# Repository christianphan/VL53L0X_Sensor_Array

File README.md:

# VL53L0X_Sensor_Array
Schematic and Cad file for array of VL53L0X for proximity sensing applications

This PCB combines 5 VL53L0X sensors adjacent next to each other to detect motion and finger gestures. An I2C multiplexor is also in the PCB to control the 5 sensors over I2C.

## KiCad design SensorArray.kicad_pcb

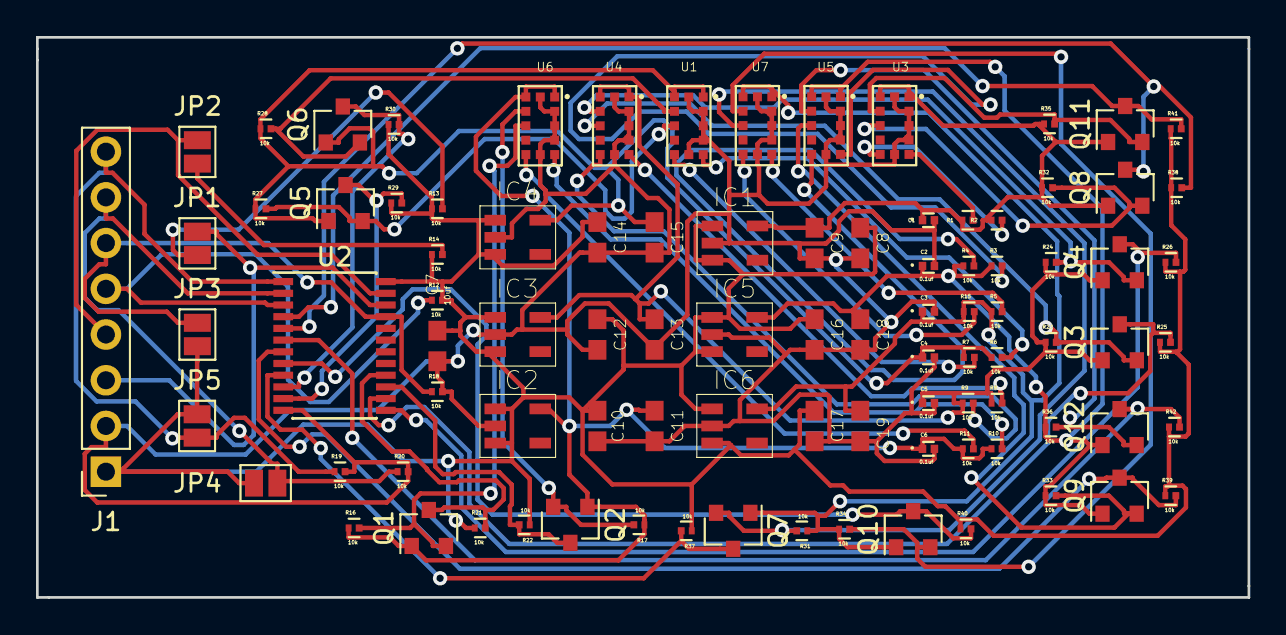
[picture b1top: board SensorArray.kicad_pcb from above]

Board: 2 copper layers, 67.3 x 31.1 mm, 92 parts (0 on the bottom side), 52 nets.

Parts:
C1, C2, C3, C4, C5, C6: 0.1uf; CAPC0603X33N
C7, C8, C9, C10, C11, C12, C13, C14, C15, C16, C17, C18, C19: 10uf; 0603-NO
IC1: MIC1; SOT95P280X130-5N
IC2: MIC6; SOT95P280X130-5N
IC3: MIC5; SOT95P280X130-5N
IC4: MIC4; SOT95P280X130-5N
IC5: MIC2; SOT95P280X130-5N
IC6: MIC3; SOT95P280X130-5N
J1: Conn_01x08; PinSocket_1x08_P2.54mm_Vertical
JP1, JP2: SolderJumper-2_P1.3mm_Open_Pad1.0x1.5mm
JP3, JP4, JP5: SolderJumper_2_Open; SolderJumper-2_P1.3mm_Open_Pad1.0x1.5mm
Q1, Q2, Q3, Q4, Q5, Q6, Q7, Q8, Q9, Q10, Q11, Q12: BSS138; SOT-23
R1, R2, R3, R4, R5, R6, R7, R8, R9, R10, R11, R12, R13, R14, R15, R16, R17, R18, R19, R20, R21, R22, R23, R24, R25, R26, R27, R28, R29, R30, R31, R32, R33, R34, R35, R36, R37, R38, R39, R40, R41, R42: 10k; RESC0603X26N
U1, U3, U4, U5, U6, U7: VL53L0X; SENSOR_VL53L0X
U2: TCA9548APWR; TSSOP-24_4.4x7.8mm_P0.65mm

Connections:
/A0: J1.6, JP3.2, R18.1, U2.21
/A1: J1.7, JP4.2, R20.1, U2.2
/A2: J1.8, JP5.1, R19.1, U2.1
/OUT_0: C1.1, C9.1, IC1.5, Q8.1, Q11.1, R1.1, R2.1, R32.1, R35.1, U3.1, U3.11
/OUT_1: C2.1, C18.1, IC5.5, Q9.1, Q12.1, R3.1, R4.1, R33.1, R36.1, U5.1, U5.11
/OUT_2: C3.1, C19.1, IC6.5, Q7.1, Q10.1, R5.1, R15.1, R31.1, R34.1, U7.1, U7.11
/OUT_3: C4.1, C15.1, IC4.5, Q5.1, Q6.1, R6.1, R7.1, R27.1, R28.1, U1.1, U1.11
/OUT_4: C5.1, C13.1, IC3.5, Q3.1, Q4.1, R8.1, R9.1, R23.1, R24.1, U4.1, U4.11
/OUT_5: C6.1, C11.1, IC2.5, Q1.1, Q2.1, R10.1, R11.1, R16.1, R17.1, U6.1, U6.11
/Reset: J1.5, R12.1, U2.3
/SC0: Q11.3, R41.2, U2.4
/SC0_2.8: Q11.2, R35.2, U3.10
/SC1: Q12.3, R42.2, U2.6
/SC1_2.8: Q12.2, R36.2, U5.10
/SC2: Q10.3, R40.2, U2.8
/SC2_2.8: Q10.2, R34.2, U7.10
/SC3: Q6.3, R30.2, U2.10
/SC3_2.8: Q6.2, R28.2, U1.10
/SC4: Q4.3, R26.2, U2.13
/SC4_2.8: Q4.2, R24.2, U4.10
/SC5: Q2.3, R22.2, U2.15
/SC5_2.8: Q2.2, R17.2, U6.10
/SC_IN: J1.4, JP2.2, U2.23
/SD0: Q8.3, R38.2, U2.5
/SD0_2.8: Q8.2, R32.2, U3.9
/SD1: Q9.3, R39.2, U2.7
/SD1_2.8: Q9.2, R33.2, U5.9
/SD2: Q7.3, R37.2, U2.9
/SD2_2.8: Q7.2, R31.2, U7.9
/SD3: Q5.3, R29.2, U2.11
/SD3_2.8: Q5.2, R27.2, U1.9
/SD4: Q3.3, R25.2, U2.14
/SD4_2.8: Q3.2, R23.2, U4.9
/SD5: Q1.3, R21.2, U2.16
/SD5_2.8: Q1.2, R16.2, U6.9
/SD_IN: J1.3, JP1.2, U2.22
GND: C1.2, C2.2, C3.2, C4.2, C5.2, C6.2, C7.1, C8.2, C9.2, C10.2, C11.2, C12.2, C13.2, C14.2, C15.2, C16.2, C17.2, C18.2, C19.2, IC1.2, IC2.2, IC3.2, IC4.2, IC5.2, IC6.2, J1.2, R18.2, R19.2, R20.2, U1.2, U1.3, U1.4, U1.6, U1.12, U2.12, U3.2, U3.3, U3.4, U3.6, U3.12, U4.2, U4.3, U4.4, U4.6, U4.12, U5.2, U5.3, U5.4, U5.6, U5.12, U6.2, U6.3, U6.4, U6.6, U6.12, U7.2, U7.3, U7.4, U7.6, U7.12
unnamed: JP1.1, R13.2
unnamed: JP2.1, R14.2
unnamed: R1.2, U3.5
unnamed: R2.2, U3.7
unnamed: R3.2, U5.5
unnamed: R4.2, U5.7
unnamed: R5.2, U7.5
unnamed: R6.2, U1.5
unnamed: R7.2, U1.7
unnamed: R8.2, U4.5
unnamed: R9.2, U4.7
unnamed: R10.2, U6.5
unnamed: R11.2, U6.7
unnamed: R15.2, U7.7
VCC: C7.2, C8.1, C10.1, C12.1, C14.1, C16.1, C17.1, IC1.1, IC1.3, IC2.1, IC2.3, IC3.1, IC3.3, IC4.1, IC4.3, IC5.1, IC5.3, IC6.1, IC6.3, J1.1, JP3.1, JP4.1, JP5.2, R12.2, R13.1, R14.1, R21.1, R22.1, R25.1, R26.1, R29.1, R30.1, R37.1, R38.1, R39.1, R40.1, R41.1, R42.1, U2.24

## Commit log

2018-11-10 Week 6 Progress
2018-11-14 More Thinks finished week 7
2018-11-20 updated schematic and pcb layout
2019-01-19 pcb made
2019-01-22 pcb image added
2019-01-22 images added to readme
2019-01-26 schematic image
